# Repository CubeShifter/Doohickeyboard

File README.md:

# Doohickeyboard
A modular approach to a macropad, utilizing pogos pins for an easy to use snap on and off experience. For this design I made 5 boards, the core, a macropad, a numpad, a knob, and an oled display. This helped me learn a lot about i2c and I learned how to use openscad! Im gonna go into depth about building each one

# General
  This applies for building any board. 3d print the top and bottom case files for whichever one you choose, and put m2 heatsets in the bottom. Solder on any componentry onto the board making sure that male pogos are on the top and left, and female pogos are on the bottom and right, and sandwitch it between the top and bottom cases. Then take an m2 screw on all four sides and secure it. Put the magnets in the holes next to the pogo pins, making sure that south is for female pins and north is for male pins. Use the BOMs, use them. Also if this comes off as bad, or not thorough enough, keep in mind i am writing this at 1am in the morning, and also at 7am after being in a flight with crying babies.

#Core

Bottom

Top

Schematic

PCB

For assembling this, solder on the pogos, SMD solder the xiao, and solder on the switch. i havent added in implementation for it, but you can also do a battery for the xiao and use wireless, just make sure your polarity is correct. When it comes to actually flashing the code onto the xiao, turn it on and plug into the usb port and install [circuit python](https://circuitpython.org) onto it. Once you sucessefully install circuit python, drag the files in the firmware folder into the CIRCUITPY drive and watch it work. When plugging modules into it you will have to turn it off, plug it in and turn it back on for safety reasons.

#Macropad

Bottom

Top

Schematic 

PCB

Solder the general stuff on, print the case. For soldering the keys, solder on the hotswap sockets so you can easily switch keyboard switches. Feel free to use keyboard keys of your choice, and whatever switches you like. The keys are arranged like the WASD keys, W being copy, A being select all, S being Paste, and D being Cut. If you want to change them you can edit the code.

#Numpad!!!

Bottom

Top

PCB

Same thing as usual, solder gneral stuff, print case. Use hotswap sockets for keys. I reccomend buying a set if numpad keys as you need custom 2u keys that normally are hard to get. if ur confused on what the keys do just look at the example. As always, change them in the code if u would like. 

# Oled
Bottom

  Top
  
Extra piece

SChematic

PCB

Do general stuff. you may notice a frametop.stl. please also print that. When assembling, solder on wires to the pcb and connect them to the oled. I thin you als need to change some resistors up to config it for I2c on the oled, but check the docs on the oled about that. Once you have it wired, sandwitch the oled between the top and the extra file, and it will be nice. Currently the display only says "hai omelette" but you can edit the code to change it to your name and give it more fucntionality.

#Knob
Bottom

Top

Sch

Pcb 

Pretty normal, just find a knob so the encoder looks fine. currently it controls volume and press it to mute. nothing special at all.

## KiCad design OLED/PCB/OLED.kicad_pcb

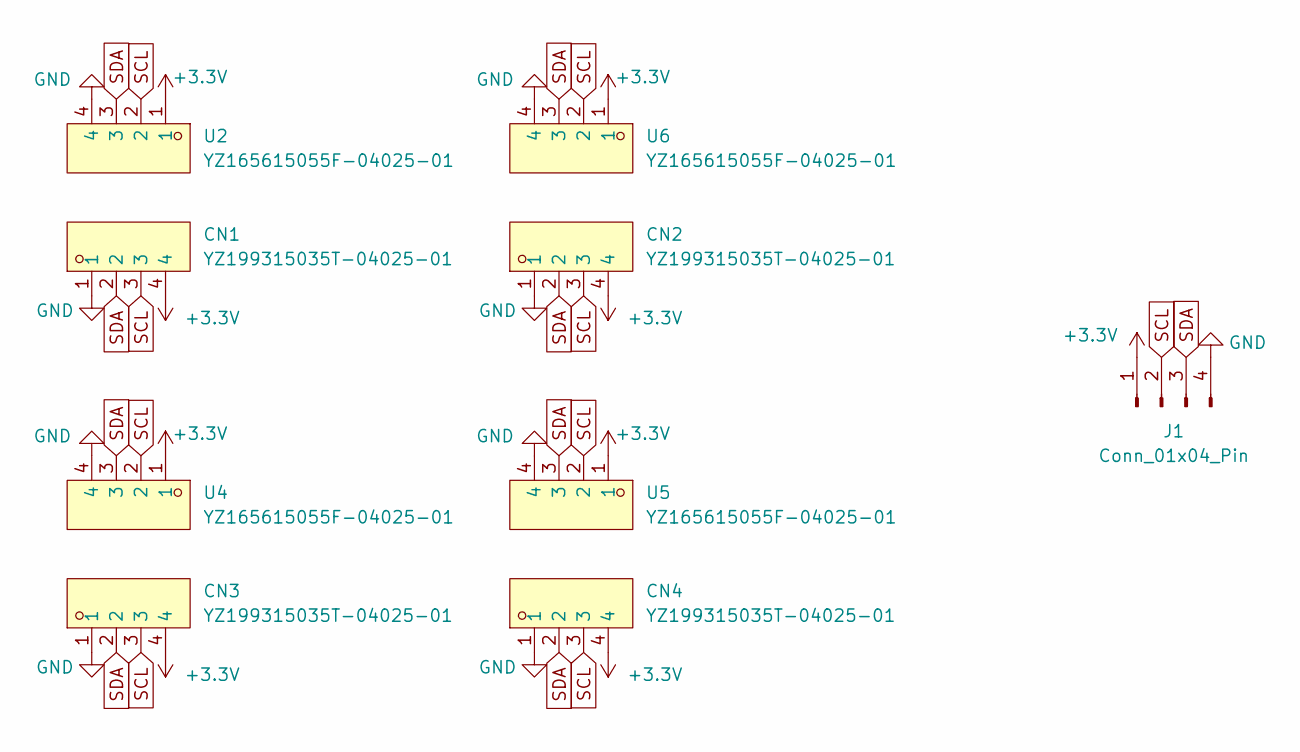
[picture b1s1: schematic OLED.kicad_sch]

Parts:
CN1, CN2, CN3, CN4: YZ199315035T-04025-01; CONN-SMD_YZ199315035T-04025-01; MPN YZ199315035T-04025-01; LCSC Part C5296825
J1: Conn_01x04_Pin; Molex_SL_171971-0004_1x04_P2.54mm_Vertical
U2, U4, U5, U6: YZ165615055F-04025-01; CONN-SMD_4P-L11.0-W5.5-P2.50_YZ165615055F-04025-01; MPN YZ165615055F-04025-01; LCSC Part C5296819

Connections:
+3.3V: CN1.4, CN2.4, CN3.4, CN4.4, J1.1, U2.1, U4.1, U5.1, U6.1
GND: CN1.1, CN2.1, CN3.1, CN4.1, J1.4, U2.4, U4.4, U5.4, U6.4
SCL: CN1.3, CN2.3, CN3.3, CN4.3, J1.2, U2.2, U4.2, U5.2, U6.2
SDA: CN1.2, CN2.2, CN3.2, CN4.2, J1.3, U2.3, U4.3, U5.3, U6.3

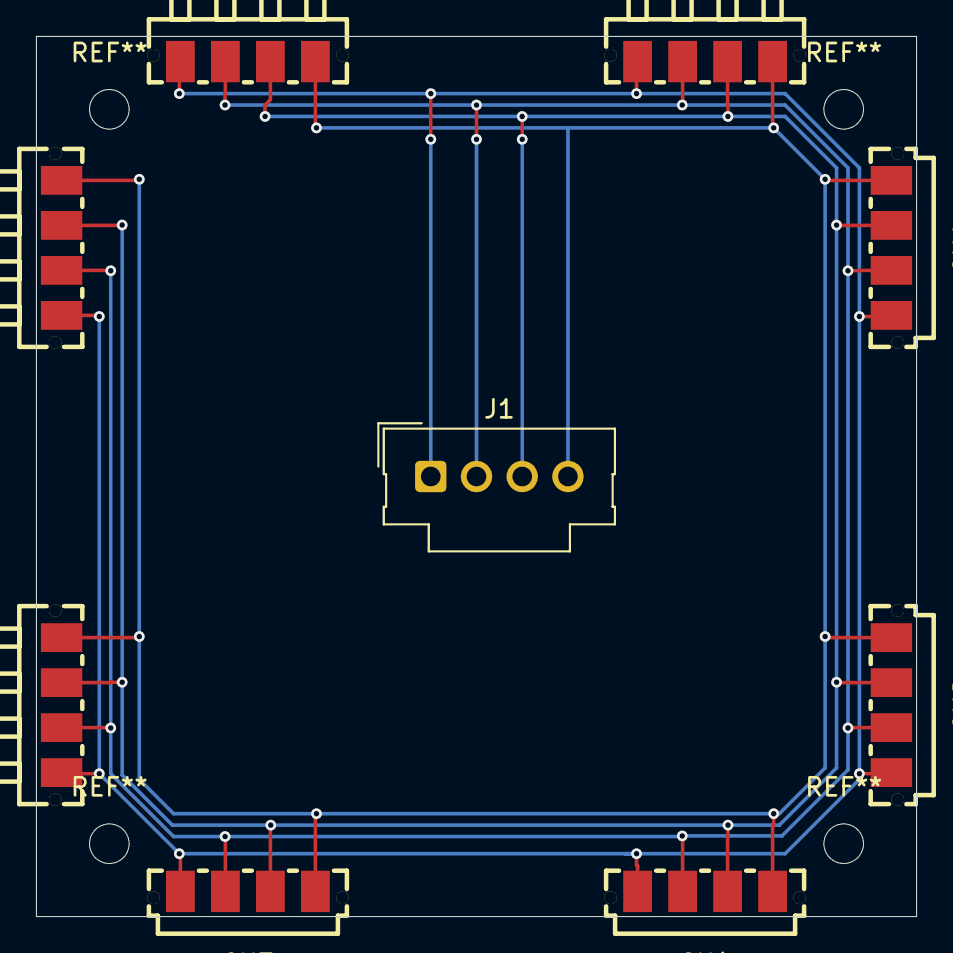
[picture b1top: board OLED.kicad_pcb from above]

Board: 2 copper layers, 48.9 x 48.9 mm, 9 parts (0 on the bottom side), 4 nets.

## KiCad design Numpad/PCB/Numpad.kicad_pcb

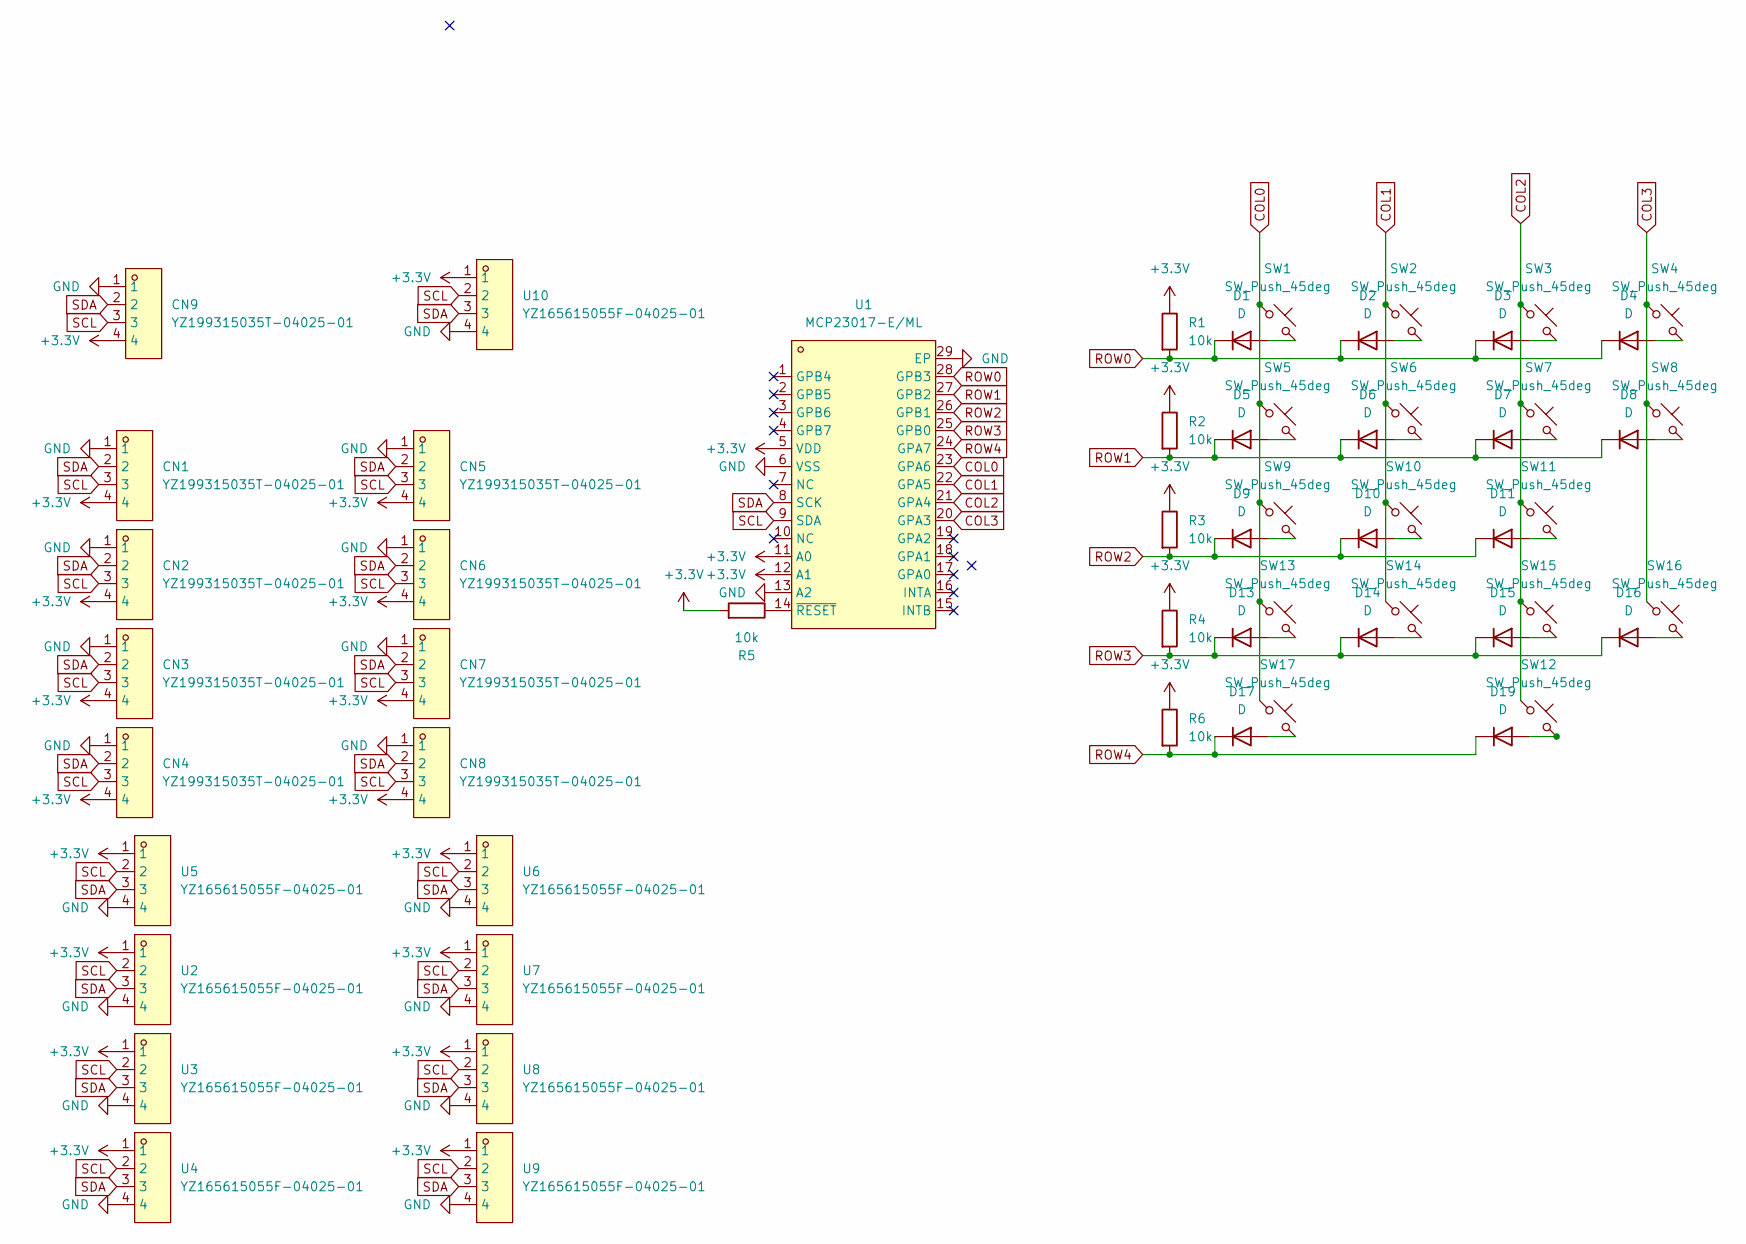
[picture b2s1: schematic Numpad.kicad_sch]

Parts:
CN1, CN2, CN4, CN5: YZ199315035T-04025-01; CONN-SMD_4P-L11.0-W5.5-P2.50_YZ165615055F-04025-01; MPN YZ199315035T-04025-01; LCSC Part C5296825
CN3, CN6, CN7, CN8, CN9: YZ199315035T-04025-01; CONN-SMD_YZ199315035T-04025-01; MPN YZ199315035T-04025-01; LCSC Part C5296825
D1, D2, D3, D4, D5, D6, D7, D8, D9, D10, D11, D13, D14, D15, D16, D17, D19: D; D_0402_1005Metric
R1, R2, R3, R4, R5, R6: 10k; R_0402_1005Metric
SW1, SW2, SW3, SW4, SW5, SW6, SW7, SW8, SW9, SW10, SW11, SW12, SW13, SW14, SW15, SW16, SW17: SW_Push_45deg; Kailh_socket_MX
U1: MCP23017-E/ML; QFN-28_L6.0-W6.0-P0.65-BL-EP3.7; MPN MCP23017-E/ML; LCSC Part C639770
U2, U6, U9, U10: YZ165615055F-04025-01; CONN-SMD_YZ199315035T-04025-01; MPN YZ165615055F-04025-01; LCSC Part C5296819
U3, U4, U5, U7, U8: YZ165615055F-04025-01; CONN-SMD_4P-L11.0-W5.5-P2.50_YZ165615055F-04025-01; MPN YZ165615055F-04025-01; LCSC Part C5296819

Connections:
+3.3V: CN1.4, CN2.4, CN3.4, CN4.4, CN5.4, CN6.4, CN7.4, CN8.4, CN9.4, R1.1, R2.1, R3.1, R4.1, R5.2, R6.1, U1.5 (VDD), U1.11 (A0), U1.12 (A1), U2.1, U3.1, U4.1, U5.1, U6.1, U7.1, U8.1, U9.1, U10.1
COL0: SW1.1, SW5.1, SW9.1, SW13.1, SW17.1, U1.23 (GPA6)
COL1: SW2.1, SW6.1, SW10.1, SW14.1, U1.22 (GPA5)
COL2: SW3.1, SW7.1, SW11.1, SW12.1, SW15.1, U1.21 (GPA4)
COL3: SW4.1, SW8.1, SW16.1, U1.20 (GPA3)
GND: CN1.1, CN2.1, CN3.1, CN4.1, CN5.1, CN6.1, CN7.1, CN8.1, CN9.1, U1.6 (VSS), U1.13 (A2), U1.29 (EP), U2.4, U3.4, U4.4, U5.4, U6.4, U7.4, U8.4, U9.4, U10.4
unnamed: D1.2 (A), SW1.2
unnamed: D2.2 (A), SW2.2
unnamed: D3.2 (A), SW3.2
unnamed: D4.2 (A), SW4.2
unnamed: D5.2 (A), SW5.2
unnamed: D6.2 (A), SW6.2
unnamed: D7.2 (A), SW7.2
unnamed: D8.2 (A), SW8.2
unnamed: D9.2 (A), SW9.2
unnamed: D10.2 (A), SW10.2
unnamed: D11.2 (A), SW11.2
unnamed: D13.2 (A), SW13.2
unnamed: D14.2 (A), SW14.2
unnamed: D15.2 (A), SW15.2
unnamed: D16.2 (A), SW16.2
unnamed: D17.2 (A), SW17.2
unnamed: D19.2 (A), SW12.2
unnamed: R5.1, U1.14 (~RESET)
ROW0: D1.1 (K), D2.1 (K), D3.1 (K), D4.1 (K), R1.2, U1.28 (GPB3)
ROW1: D5.1 (K), D6.1 (K), D7.1 (K), D8.1 (K), R2.2, U1.27 (GPB2)
ROW2: D9.1 (K), D10.1 (K), D11.1 (K), R3.2, U1.26 (GPB1)
ROW3: D13.1 (K), D14.1 (K), D15.1 (K), D16.1 (K), R4.2, U1.25 (GPB0)
ROW4: D17.1 (K), D19.1 (K), R6.2, U1.24 (GPA7)
SCL: CN1.3, CN2.3, CN3.3, CN4.3, CN5.3, CN6.3, CN7.3, CN8.3, CN9.3, U1.9 (SDA), U2.2, U3.2, U4.2, U5.2, U6.2, U7.2, U8.2, U9.2, U10.2
SDA: CN1.2, CN2.2, CN3.2, CN4.2, CN5.2, CN6.2, CN7.2, CN8.2, CN9.2, U1.8 (SCK), U2.3, U3.3, U4.3, U5.3, U6.3, U7.3, U8.3, U9.3, U10.3

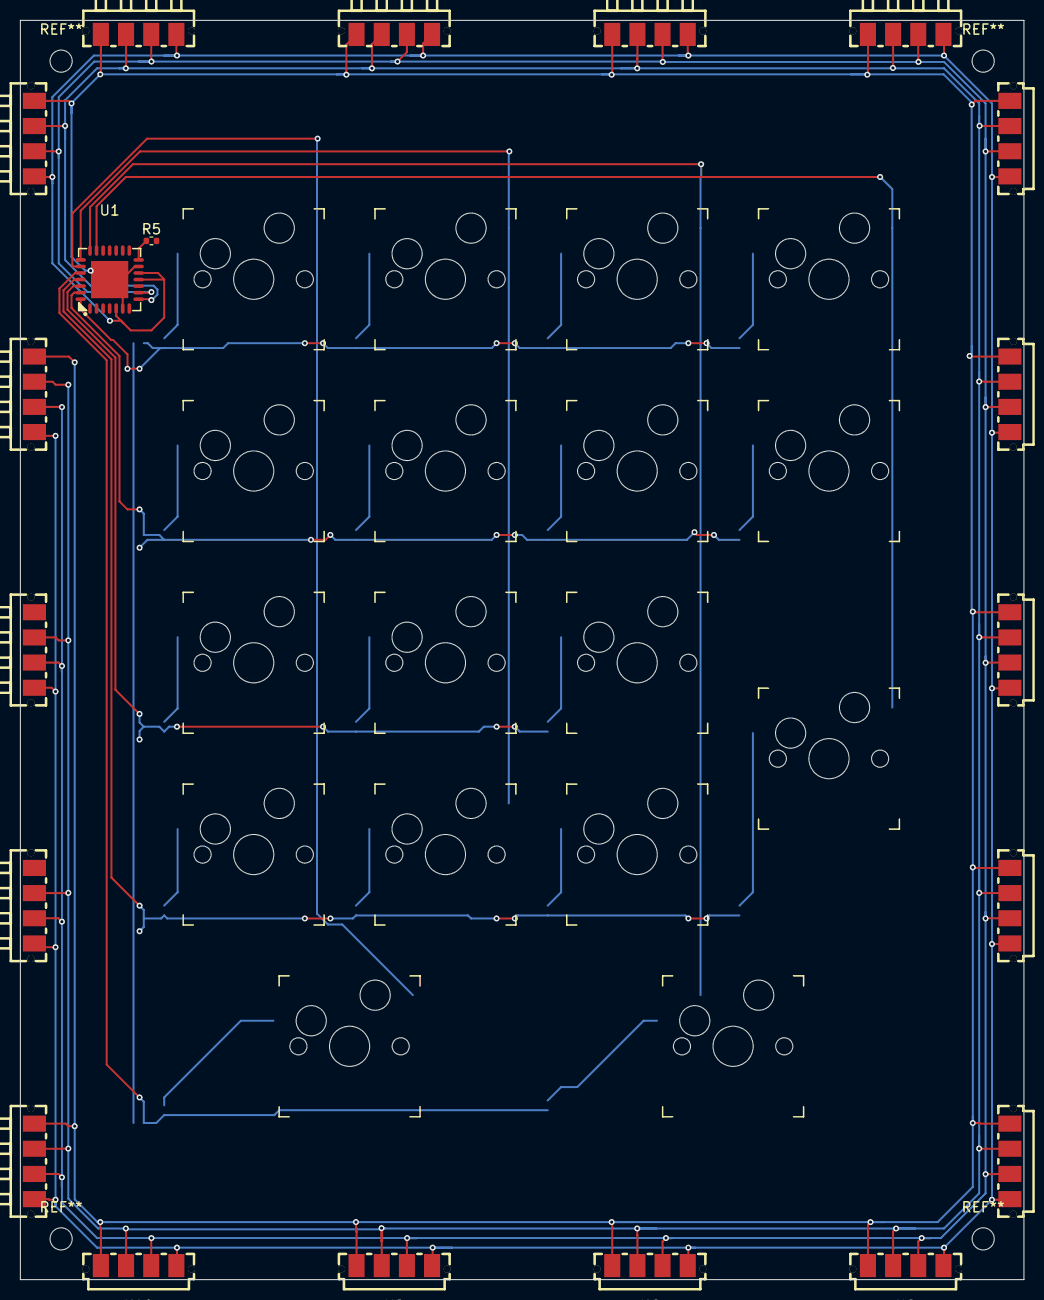
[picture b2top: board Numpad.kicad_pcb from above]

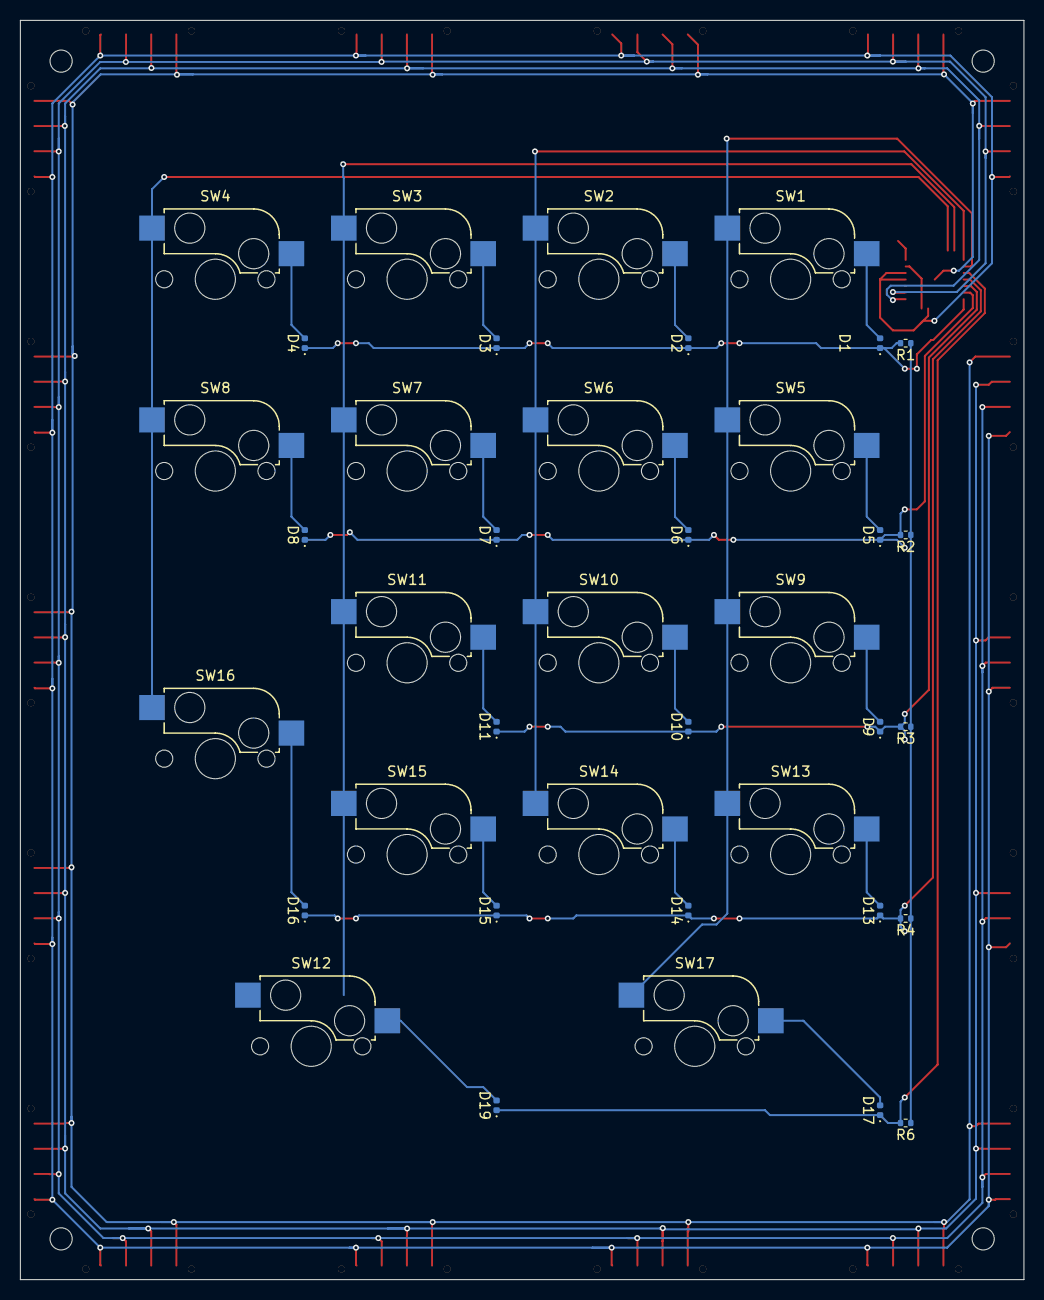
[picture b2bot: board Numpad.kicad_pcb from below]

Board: 2 copper layers, 99.7 x 125.1 mm, 59 parts (22 on the bottom side), 31 nets.

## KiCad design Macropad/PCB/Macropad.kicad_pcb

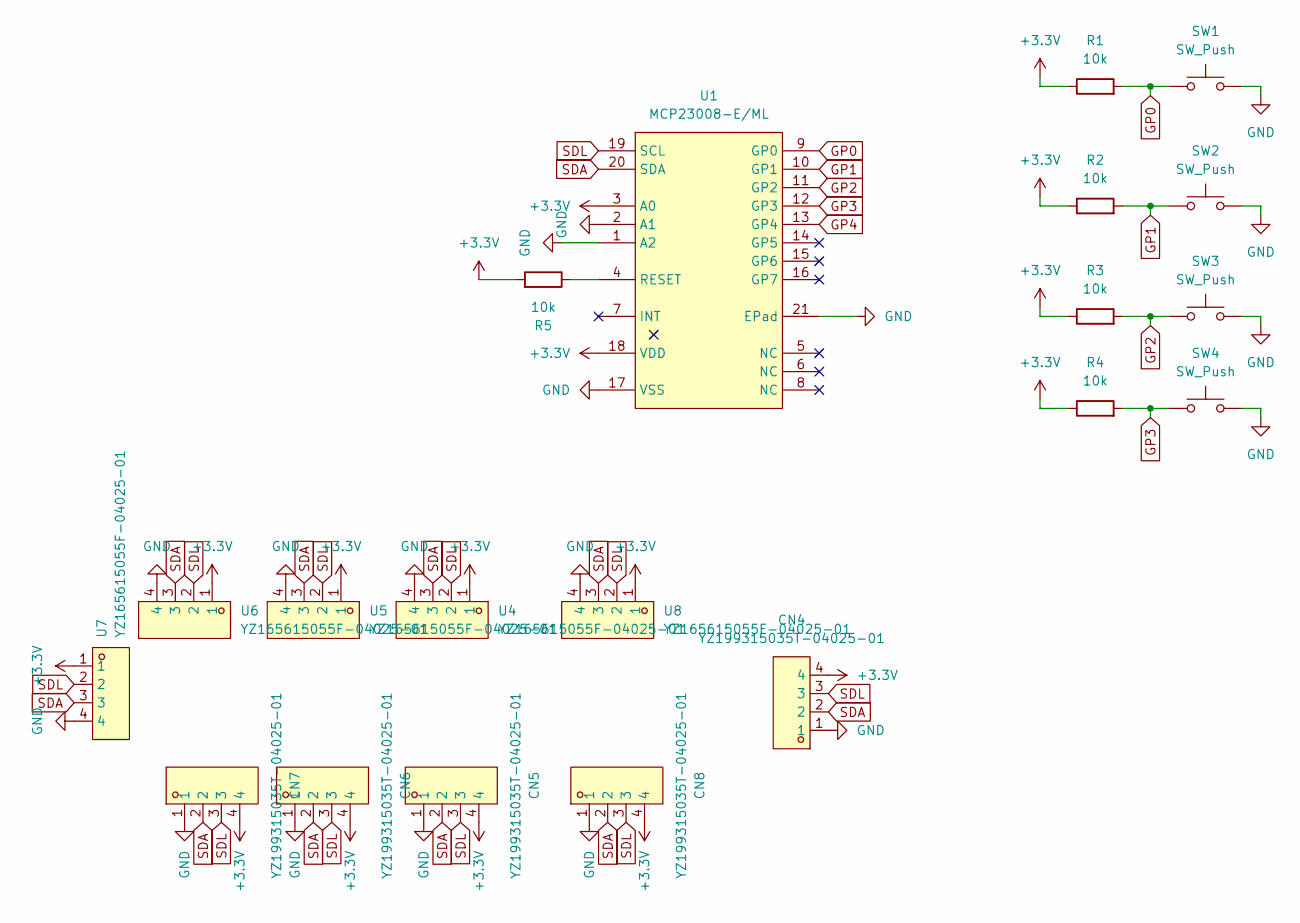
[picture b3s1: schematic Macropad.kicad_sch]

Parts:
CN4, CN5, CN6, CN7, CN8: YZ199315035T-04025-01; CONN-SMD_YZ199315035T-04025-01; MPN YZ199315035T-04025-01; LCSC Part C5296825
R1, R2, R3, R4, R5: 10k; R_0402_1005Metric
SW1, SW2, SW3, SW4: SW_Push; SW_Cherry_MX_1.00u_PCB
U1: MCP23008-E/ML; QFN-20_L4.0-W4.0-P0.50-BL-EP2.7; MPN MCP23008-E/ML; LCSC Part C144211
U4, U5, U6, U7, U8: YZ165615055F-04025-01; CONN-SMD_4P-L11.0-W5.5-P2.50_YZ165615055F-04025-01; MPN YZ165615055F-04025-01; LCSC Part C5296819

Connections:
+3.3V: CN4.4, CN5.4, CN6.4, CN7.4, CN8.4, R1.1, R2.1, R3.1, R4.1, R5.2, U1.3 (A0), U1.18 (VDD), U4.1, U5.1, U6.1, U7.1, U8.1
GND: CN4.1, CN5.1, CN6.1, CN7.1, CN8.1, SW1.2, SW2.2, SW3.2, SW4.2, U1.1 (A2), U1.2 (A1), U1.17 (VSS), U1.21 (EPad), U4.4, U5.4, U6.4, U7.4, U8.4
GP0: R1.2, SW1.1, U1.9 (GP0)
GP1: R2.2, SW2.1, U1.10 (GP1)
GP2: R3.2, SW3.1, U1.11 (GP2)
GP3: R4.2, SW4.1, U1.12 (GP3)
GP4: U1.13 (GP4)
unnamed: R5.1, U1.4 (RESET)
SDA: CN4.2, CN5.2, CN6.2, CN7.2, CN8.2, U1.20 (SDA), U4.3, U5.3, U6.3, U7.3, U8.3
SDL: CN4.3, CN5.3, CN6.3, CN7.3, CN8.3, U1.19 (SCL), U4.2, U5.2, U6.2, U7.2, U8.2

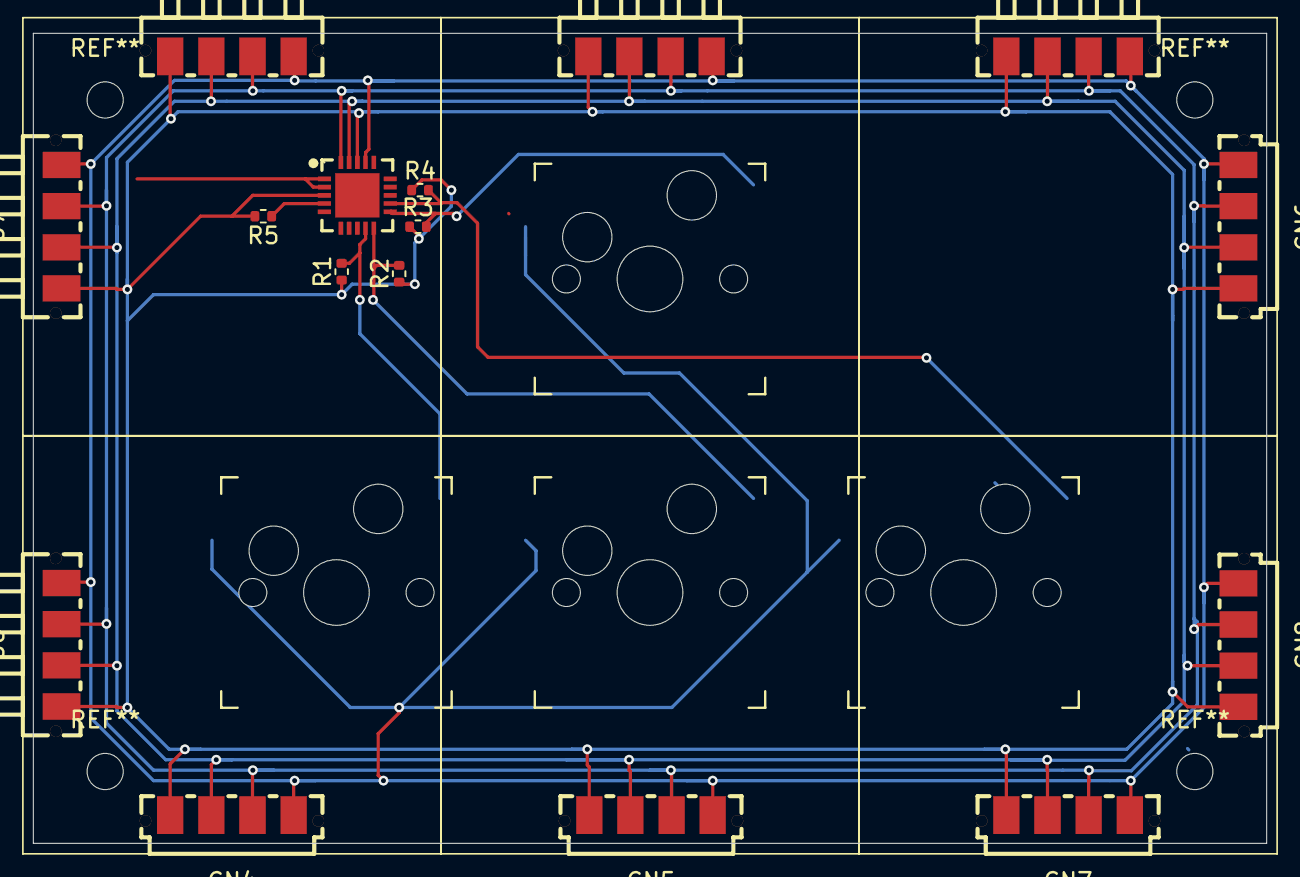
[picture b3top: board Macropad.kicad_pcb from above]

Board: 2 copper layers, 74.9 x 49.2 mm, 20 parts (0 on the bottom side), 9 nets.

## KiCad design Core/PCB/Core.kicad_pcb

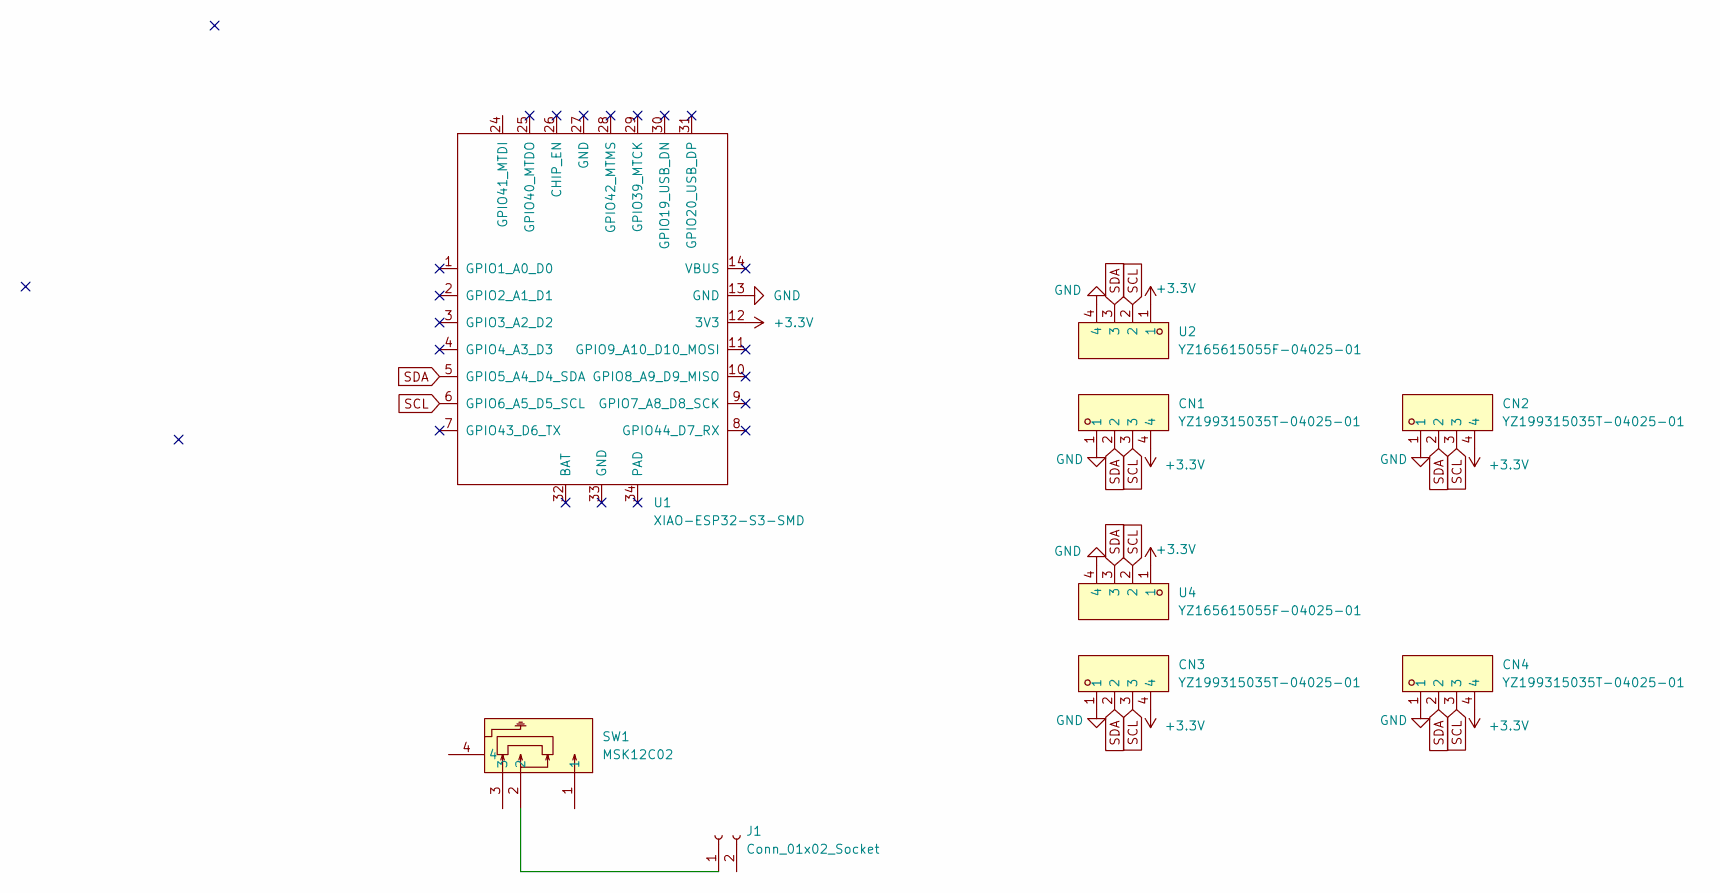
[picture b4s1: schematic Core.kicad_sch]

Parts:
CN1, CN2, CN3, CN4: YZ199315035T-04025-01; CONN-SMD_YZ199315035T-04025-01; MPN YZ199315035T-04025-01; LCSC Part C5296825
J1: Conn_01x02_Socket; PinHeader_1x02_P2.54mm_Vertical
SW1: MSK12C02; SW-TH_MSK12C02; MPN MSK12C02; LCSC Part C431540
U1: XIAO-ESP32-S3-SMD
U2, U4: YZ165615055F-04025-01; CONN-SMD_4P-L11.0-W5.5-P2.50_YZ165615055F-04025-01; MPN YZ165615055F-04025-01; LCSC Part C5296819

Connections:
+3.3V: CN1.4, CN2.4, CN3.4, CN4.4, U1.12 (3V3), U2.1, U4.1
BAT+: SW1.1, U1.23
BAT-: J1.2, U1.24 (GPIO41_MTDI)
GND: CN1.1, CN2.1, CN3.1, CN4.1, U1.13 (GND), U2.4, U4.4
unnamed: J1.1, SW1.2
SCL: CN1.3, CN2.3, CN3.3, CN4.3, U1.6 (GPIO6_A5_D5_SCL), U2.2, U4.2
SDA: CN1.2, CN2.2, CN3.2, CN4.2, U1.5 (GPIO5_A4_D4_SDA), U2.3, U4.3

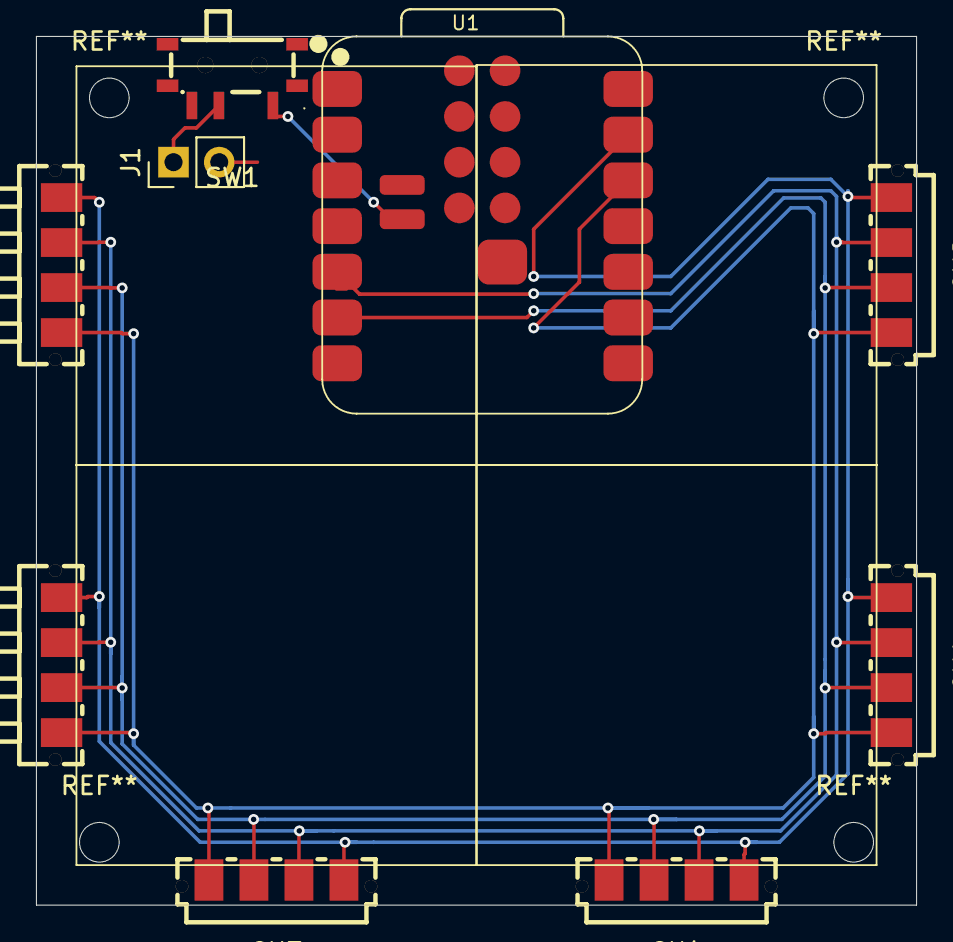
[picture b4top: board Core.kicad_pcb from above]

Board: 2 copper layers, 48.9 x 48.3 mm, 9 parts (0 on the bottom side), 7 nets.

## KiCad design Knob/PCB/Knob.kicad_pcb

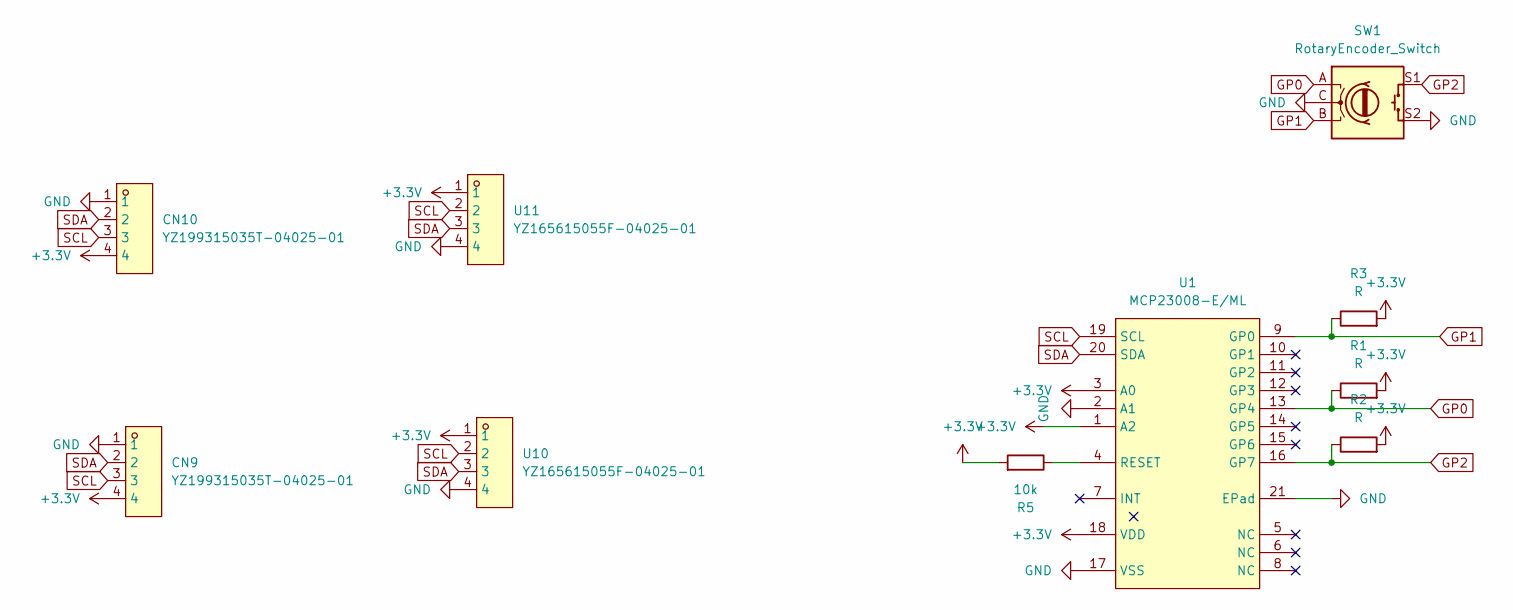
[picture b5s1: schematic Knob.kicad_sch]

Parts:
CN9, CN10: YZ199315035T-04025-01; CONN-SMD_YZ199315035T-04025-01; MPN YZ199315035T-04025-01; LCSC Part C5296825
R1, R2, R3: R; R_0402_1005Metric
R5: 10k; R_0402_1005Metric
SW1: RotaryEncoder_Switch; RotaryEncoder_Alps_EC11E-Switch_Vertical_H20mm
U1: MCP23008-E/ML; QFN-20_L4.0-W4.0-P0.50-BL-EP2.7; MPN MCP23008-E/ML; LCSC Part C144211
U10, U11: YZ165615055F-04025-01; CONN-SMD_4P-L11.0-W5.5-P2.50_YZ165615055F-04025-01; MPN YZ165615055F-04025-01; LCSC Part C5296819

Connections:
+3.3V: CN9.4, CN10.4, R1.2, R2.2, R3.2, R5.2, U1.1 (A2), U1.3 (A0), U1.18 (VDD), U10.1, U11.1
GND: CN9.1, CN10.1, SW1.C, SW1.S2, U1.2 (A1), U1.17 (VSS), U1.21 (EPad), U10.4, U11.4
GP0: R1.1, SW1.A, U1.13 (GP4)
GP1: R3.1, SW1.B, U1.9 (GP0)
GP2: R2.1, SW1.S1, U1.16 (GP7)
unnamed: R5.1, U1.4 (RESET)
SCL: CN9.3, CN10.3, U1.19 (SCL), U10.2, U11.2
SDA: CN9.2, CN10.2, U1.20 (SDA), U10.3, U11.3

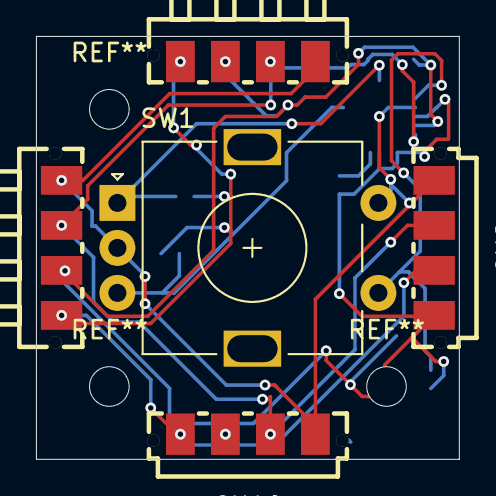
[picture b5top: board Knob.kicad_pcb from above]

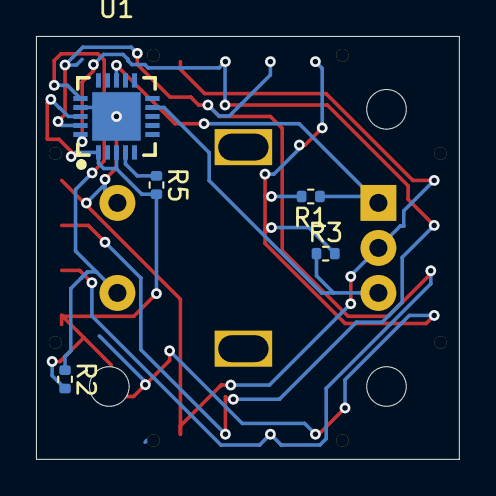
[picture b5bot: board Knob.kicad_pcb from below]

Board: 2 copper layers, 23.5 x 23.5 mm, 10 parts (5 on the bottom side), 8 nets.
